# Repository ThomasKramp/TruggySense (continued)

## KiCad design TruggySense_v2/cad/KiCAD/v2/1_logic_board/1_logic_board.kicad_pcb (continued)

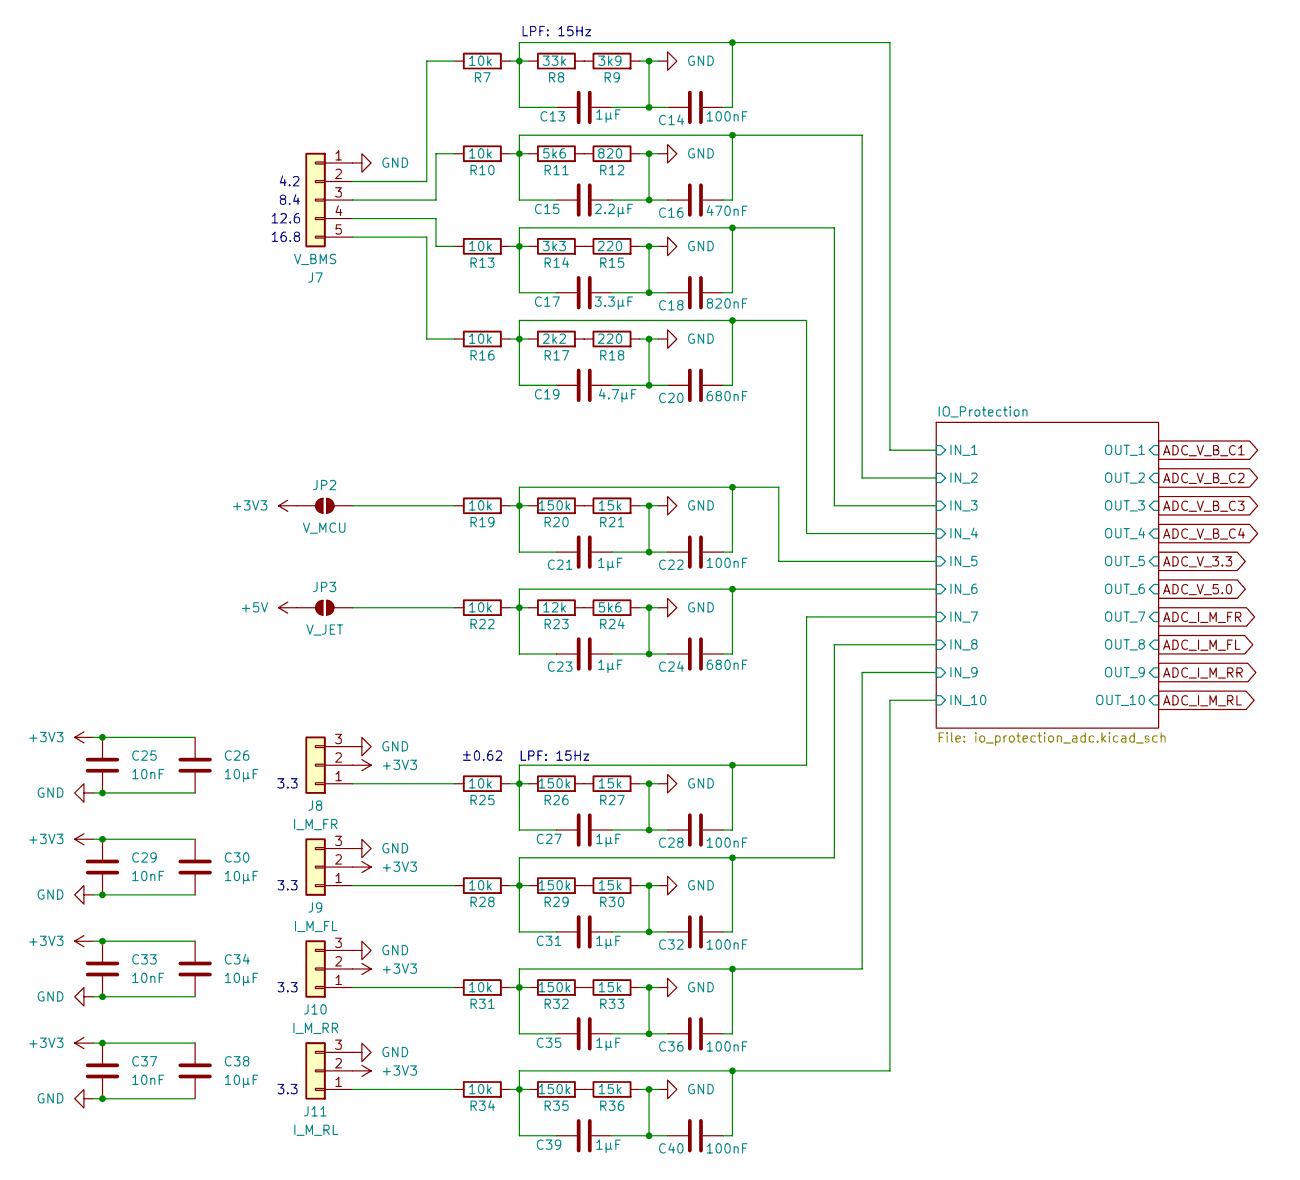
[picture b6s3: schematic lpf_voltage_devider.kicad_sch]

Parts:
C13, C21, C23, C27, C31, C35, C39: 1µF; C_0805_2012Metric_Pad1.18x1.45mm_HandSolder
C14, C22, C28, C32, C36, C40: 100nF; C_0805_2012Metric_Pad1.18x1.45mm_HandSolder
C15: 2.2µF; C_0805_2012Metric_Pad1.18x1.45mm_HandSolder
C16: 470nF; C_0805_2012Metric_Pad1.18x1.45mm_HandSolder
C17: 3.3µF; C_0805_2012Metric_Pad1.18x1.45mm_HandSolder
C18: 820nF; C_0805_2012Metric_Pad1.18x1.45mm_HandSolder
C19: 4.7µF; C_0805_2012Metric_Pad1.18x1.45mm_HandSolder
C20, C24: 680nF; C_0805_2012Metric_Pad1.18x1.45mm_HandSolder
C25, C29, C33, C37: 10nF; C_0805_2012Metric_Pad1.18x1.45mm_HandSolder
C26, C30, C34, C38: 10µF; C_0805_2012Metric_Pad1.18x1.45mm_HandSolder
J7: V_BMS; JST_XH_B5B-XH-A_1x05_P2.50mm_Vertical
J8: I_M_FR; JST_XH_B3B-XH-A_1x03_P2.50mm_Vertical
J9: I_M_FL; JST_XH_B3B-XH-A_1x03_P2.50mm_Vertical
J10: I_M_RR; JST_XH_B3B-XH-A_1x03_P2.50mm_Vertical
J11: I_M_RL; JST_XH_B3B-XH-A_1x03_P2.50mm_Vertical
JP2: V_MCU; SolderJumper-2_P1.3mm_Open_RoundedPad1.0x1.5mm
JP3: V_JET; SolderJumper-2_P1.3mm_Open_RoundedPad1.0x1.5mm
R7, R10, R13, R16, R19, R22, R25, R28, R31, R34: 10k; R_0805_2012Metric_Pad1.20x1.40mm_HandSolder
R8: 33k; R_0805_2012Metric_Pad1.20x1.40mm_HandSolder
R9: 3k9; R_0805_2012Metric_Pad1.20x1.40mm_HandSolder
R11, R24: 5k6; R_0805_2012Metric_Pad1.20x1.40mm_HandSolder
R12: 820; R_0805_2012Metric_Pad1.20x1.40mm_HandSolder
R14: 3k3; R_0805_2012Metric_Pad1.20x1.40mm_HandSolder
R15, R18: 220; R_0805_2012Metric_Pad1.20x1.40mm_HandSolder
R17: 2k2; R_0805_2012Metric_Pad1.20x1.40mm_HandSolder
R20, R26, R29, R32, R35: 150k; R_0805_2012Metric_Pad1.20x1.40mm_HandSolder
R21, R27, R30, R33, R36: 15k; R_0805_2012Metric_Pad1.20x1.40mm_HandSolder
R23: 12k; R_0805_2012Metric_Pad1.20x1.40mm_HandSolder

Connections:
+3V3: C25.1, C26.1, C29.1, C30.1, C33.1, C34.1, C37.1, C38.1, J8.2, J9.2, J10.2, J11.2, JP2.2 (B); also elsewhere on the board
+5V: JP3.2 (B); also elsewhere on the board
/ADC/IO_Protection/IN_1: C13.1, C14.1, R7.2, R8.1; also elsewhere on the board
/ADC/IO_Protection/IN_2: C15.1, C16.1, R10.2, R11.1; also elsewhere on the board
/ADC/IO_Protection/IN_3: C17.1, C18.1, R13.2, R14.1; also elsewhere on the board
/ADC/IO_Protection/IN_4: C19.1, C20.1, R16.2, R17.1; also elsewhere on the board
/ADC/IO_Protection/IN_5: C21.2, C22.1, R19.2, R20.1; also elsewhere on the board
/ADC/IO_Protection/IN_6: C23.2, C24.1, R22.2, R23.1; also elsewhere on the board
/ADC/IO_Protection/IN_7: C27.1, C28.1, R25.2, R26.1; also elsewhere on the board
/ADC/IO_Protection/IN_8: C31.1, C32.1, R28.2, R29.1; also elsewhere on the board
/ADC/IO_Protection/IN_9: C35.1, C36.1, R31.2, R32.1; also elsewhere on the board
/ADC/IO_Protection/IN_10: C39.1, C40.1, R34.2, R35.1; also elsewhere on the board
GND: C13.2, C14.2, C15.2, C16.2, C17.2, C18.2, C19.2, C20.2, C21.1, C22.2, C23.1, C24.2, C25.2, C26.2, C27.2, C28.2, C29.2, C30.2, C31.2, C32.2, C33.2, C34.2, C35.2, C36.2, C37.2, C38.2, C39.2, C40.2, J7.1, J8.3, J9.3, J10.3, J11.3, R9.2, R12.2, R15.2, R18.2, R21.2, R24.2, R27.2, R30.2, R33.2, R36.2; also elsewhere on the board
unnamed: J7.2, R7.1
unnamed: J7.3, R10.1
unnamed: J7.4, R13.1
unnamed: J7.5, R16.1
unnamed: J8.1, R25.1
unnamed: J9.1, R28.1
unnamed: J10.1, R31.1
unnamed: J11.1, R34.1
unnamed: JP2.1 (A), R19.1
unnamed: JP3.1 (A), R22.1
unnamed: R8.2, R9.1
unnamed: R11.2, R12.1
unnamed: R14.2, R15.1
unnamed: R17.2, R18.1
unnamed: R20.2, R21.1
unnamed: R23.2, R24.1
unnamed: R26.2, R27.1
unnamed: R29.2, R30.1
unnamed: R32.2, R33.1
unnamed: R35.2, R36.1

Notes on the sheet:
8.4
LPF: 15Hz
3.3
16.8
±0.62
12.6
4.2

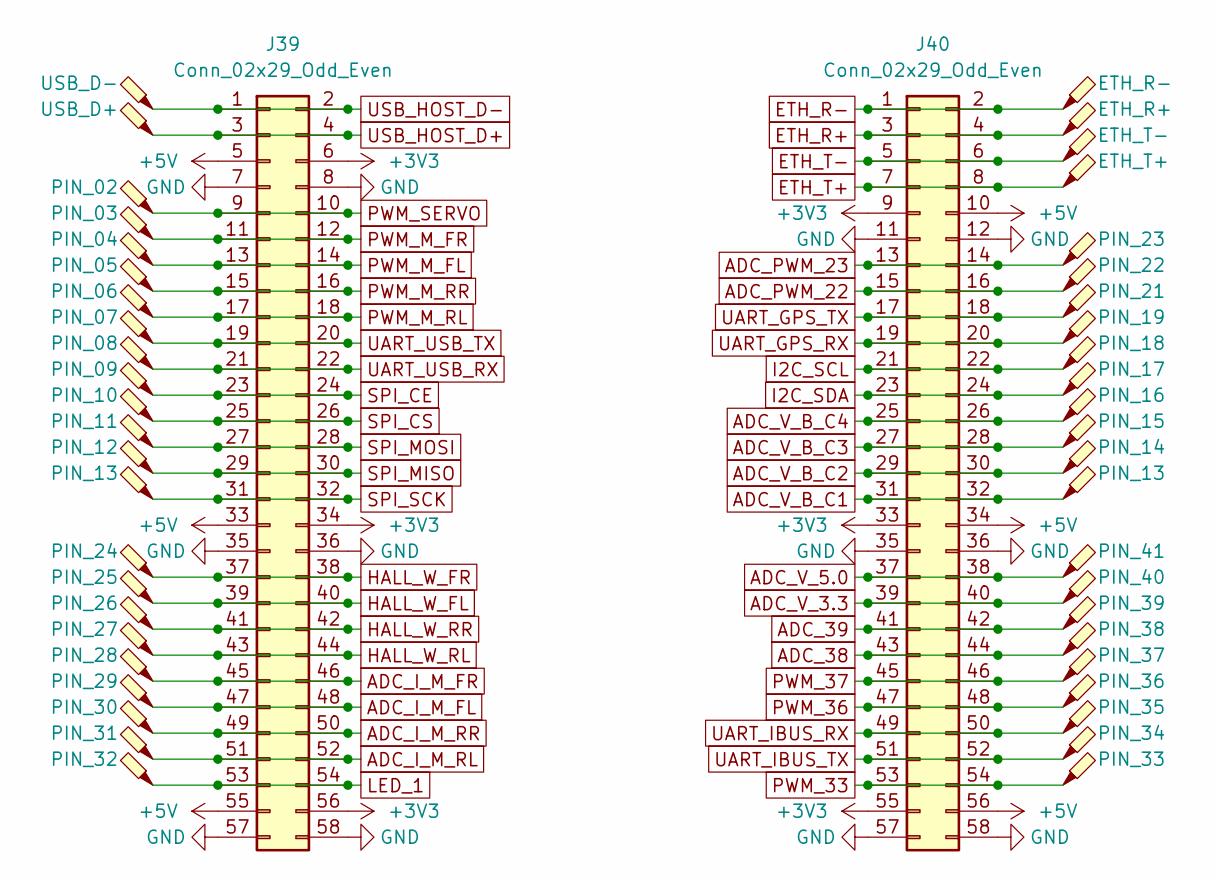
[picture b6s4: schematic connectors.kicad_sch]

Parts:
J39, J40: Conn_02x29_Odd_Even; PinHeader_2x29_P2.54mm_Vertical
TP1: USB_D-; Pin_D1.3mm_L11.0mm
TP2: ETH_R-; Pin_D1.3mm_L11.0mm
TP3: USB_D+; Pin_D1.3mm_L11.0mm
TP4: ETH_R+; Pin_D1.3mm_L11.0mm
TP5: ETH_T-; Pin_D1.3mm_L11.0mm
TP6: ETH_T+; Pin_D1.3mm_L11.0mm
TP7: PIN_02; Pin_D1.3mm_L11.0mm
TP8: PIN_03; Pin_D1.3mm_L11.0mm
TP9: PIN_04; Pin_D1.3mm_L11.0mm
TP10: PIN_23; Pin_D1.3mm_L11.0mm
TP11: PIN_05; Pin_D1.3mm_L11.0mm
TP12: PIN_22; Pin_D1.3mm_L11.0mm
TP13: PIN_06; Pin_D1.3mm_L11.0mm
TP14: PIN_21; Pin_D1.3mm_L11.0mm
TP15: PIN_07; Pin_D1.3mm_L11.0mm
TP16: PIN_19; Pin_D1.3mm_L11.0mm
TP17: PIN_08; Pin_D1.3mm_L11.0mm
TP18: PIN_18; Pin_D1.3mm_L11.0mm
TP19: PIN_09; Pin_D1.3mm_L11.0mm
TP20: PIN_17; Pin_D1.3mm_L11.0mm
TP21: PIN_10; Pin_D1.3mm_L11.0mm
TP22: PIN_16; Pin_D1.3mm_L11.0mm
TP23: PIN_11; Pin_D1.3mm_L11.0mm
TP24: PIN_15; Pin_D1.3mm_L11.0mm
TP25: PIN_12; Pin_D1.3mm_L11.0mm
TP26: PIN_14; Pin_D1.3mm_L11.0mm
TP27, TP28: PIN_13; Pin_D1.3mm_L11.0mm
TP29: PIN_24; Pin_D1.3mm_L11.0mm
TP30: PIN_41; Pin_D1.3mm_L11.0mm
TP31: PIN_25; Pin_D1.3mm_L11.0mm
TP32: PIN_40; Pin_D1.3mm_L11.0mm
TP33: PIN_26; Pin_D1.3mm_L11.0mm
TP34: PIN_39; Pin_D1.3mm_L11.0mm
TP35: PIN_27; Pin_D1.3mm_L11.0mm
TP36: PIN_38; Pin_D1.3mm_L11.0mm
TP37: PIN_28; Pin_D1.3mm_L11.0mm
TP38: PIN_37; Pin_D1.3mm_L11.0mm
TP39: PIN_29; Pin_D1.3mm_L11.0mm
TP40: PIN_36; Pin_D1.3mm_L11.0mm
TP41: PIN_30; Pin_D1.3mm_L11.0mm
TP42: PIN_35; Pin_D1.3mm_L11.0mm
TP43: PIN_31; Pin_D1.3mm_L11.0mm
TP44: PIN_34; Pin_D1.3mm_L11.0mm
TP45: PIN_32; Pin_D1.3mm_L11.0mm
TP46: PIN_33; Pin_D1.3mm_L11.0mm

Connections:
+3V3: J39.6, J39.34, J39.56, J40.9, J40.33, J40.55; also elsewhere on the board
+5V: J39.5, J39.33, J39.55, J40.10, J40.34, J40.56; also elsewhere on the board
ADC_38: J40.43, J40.44, TP36.1; also elsewhere on the board
ADC_39: J40.41, J40.42, TP34.1; also elsewhere on the board
ADC_I_M_FL: J39.47, J39.48, TP39.1; also elsewhere on the board
ADC_I_M_FR: J39.45, J39.46, TP37.1; also elsewhere on the board
ADC_I_M_RL: J39.51, J39.52, TP43.1; also elsewhere on the board
ADC_I_M_RR: J39.49, J39.50, TP41.1; also elsewhere on the board
ADC_PWM_22: J40.15, J40.16, TP12.1; also elsewhere on the board
ADC_PWM_23: J40.13, J40.14, TP10.1; also elsewhere on the board
ADC_V_3.3: J40.39, J40.40, TP32.1; also elsewhere on the board
ADC_V_5.0: J40.37, J40.38, TP30.1; also elsewhere on the board
ADC_V_B_C1: J40.31, J40.32, TP28.1; also elsewhere on the board
ADC_V_B_C2: J40.29, J40.30, TP26.1; also elsewhere on the board
ADC_V_B_C3: J40.27, J40.28, TP24.1; also elsewhere on the board
ADC_V_B_C4: J40.25, J40.26, TP22.1; also elsewhere on the board
ETH_R+: J40.3, J40.4, TP4.1; also elsewhere on the board
ETH_R-: J40.1, J40.2, TP2.1; also elsewhere on the board
ETH_T+: J40.7, J40.8, TP6.1; also elsewhere on the board
ETH_T-: J40.5, J40.6, TP5.1; also elsewhere on the board
GND: J39.7, J39.8, J39.35, J39.36, J39.57, J39.58, J40.11, J40.12, J40.35, J40.36, J40.57, J40.58; also elsewhere on the board
HALL_W_FL: J39.39, J39.40, TP31.1; also elsewhere on the board
HALL_W_FR: J39.37, J39.38, TP29.1; also elsewhere on the board
HALL_W_RL: J39.43, J39.44, TP35.1; also elsewhere on the board
HALL_W_RR: J39.41, J39.42, TP33.1; also elsewhere on the board
I2C_SCL: J40.21, J40.22, TP18.1; also elsewhere on the board
I2C_SDA: J40.23, J40.24, TP20.1; also elsewhere on the board
LED_1: J39.53, J39.54, TP45.1; also elsewhere on the board
PWM_33: J40.53, J40.54, TP46.1; also elsewhere on the board
PWM_36: J40.47, J40.48, TP40.1; also elsewhere on the board
PWM_37: J40.45, J40.46, TP38.1; also elsewhere on the board
PWM_M_FL: J39.13, J39.14, TP9.1; also elsewhere on the board
PWM_M_FR: J39.11, J39.12, TP8.1; also elsewhere on the board
PWM_M_RL: J39.17, J39.18, TP13.1; also elsewhere on the board
PWM_M_RR: J39.15, J39.16, TP11.1; also elsewhere on the board
PWM_SERVO: J39.9, J39.10, TP7.1; also elsewhere on the board
SPI_CE: J39.23, J39.24, TP19.1; also elsewhere on the board
SPI_CS: J39.25, J39.26, TP21.1; also elsewhere on the board
SPI_MISO: J39.29, J39.30, TP25.1; also elsewhere on the board
SPI_MOSI: J39.27, J39.28, TP23.1; also elsewhere on the board
SPI_SCK: J39.31, J39.32, TP27.1; also elsewhere on the board
UART_GPS_RX: J40.19, J40.20, TP16.1; also elsewhere on the board
UART_GPS_TX: J40.17, J40.18, TP14.1; also elsewhere on the board
UART_IBUS_RX: J40.49, J40.50, TP42.1; also elsewhere on the board
UART_IBUS_TX: J40.51, J40.52, TP44.1; also elsewhere on the board
UART_USB_RX: J39.21, J39.22, TP17.1; also elsewhere on the board
UART_USB_TX: J39.19, J39.20, TP15.1; also elsewhere on the board
USB_HOST_D+: J39.3, J39.4, TP3.1; also elsewhere on the board
USB_HOST_D-: J39.1, J39.2, TP1.1; also elsewhere on the board

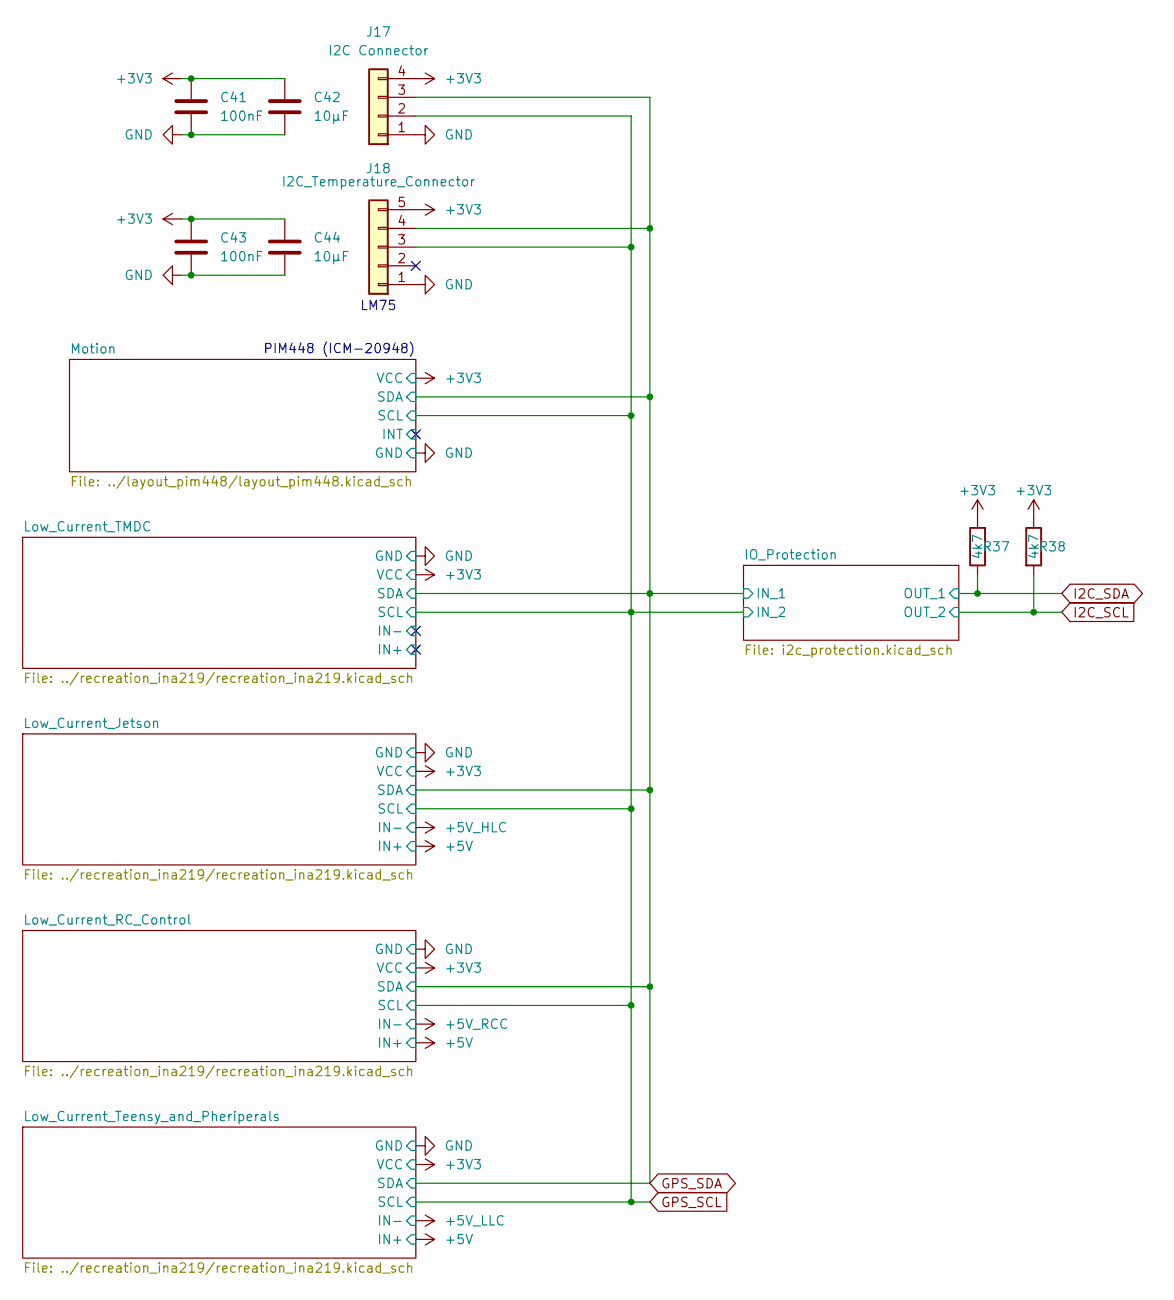
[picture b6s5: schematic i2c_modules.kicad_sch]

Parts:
C41, C43: 100nF; C_0805_2012Metric_Pad1.18x1.45mm_HandSolder
C42, C44: 10µF; C_0805_2012Metric_Pad1.18x1.45mm_HandSolder
J17: I2C Connector; JST_XH_B4B-XH-A_1x04_P2.50mm_Vertical
J18: I2C_Temperature_Connector; JST_XH_B5B-XH-A_1x05_P2.50mm_Vertical
R37, R38: 4k7; R_0805_2012Metric_Pad1.20x1.40mm_HandSolder

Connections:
+3V3: C41.1, C42.1, C43.1, C44.1, J17.4, J18.5, R37.2, R38.1; also elsewhere on the board
GND: C41.2, C42.2, C43.2, C44.2, J17.1, J18.1; also elsewhere on the board
GPS_SCL: J17.2, J18.3; also elsewhere on the board
GPS_SDA: J17.3, J18.4; also elsewhere on the board
I2C_SCL: R38.2; also elsewhere on the board
I2C_SDA: R37.1; also elsewhere on the board

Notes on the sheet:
PIM448 (ICM-20948)
LM75

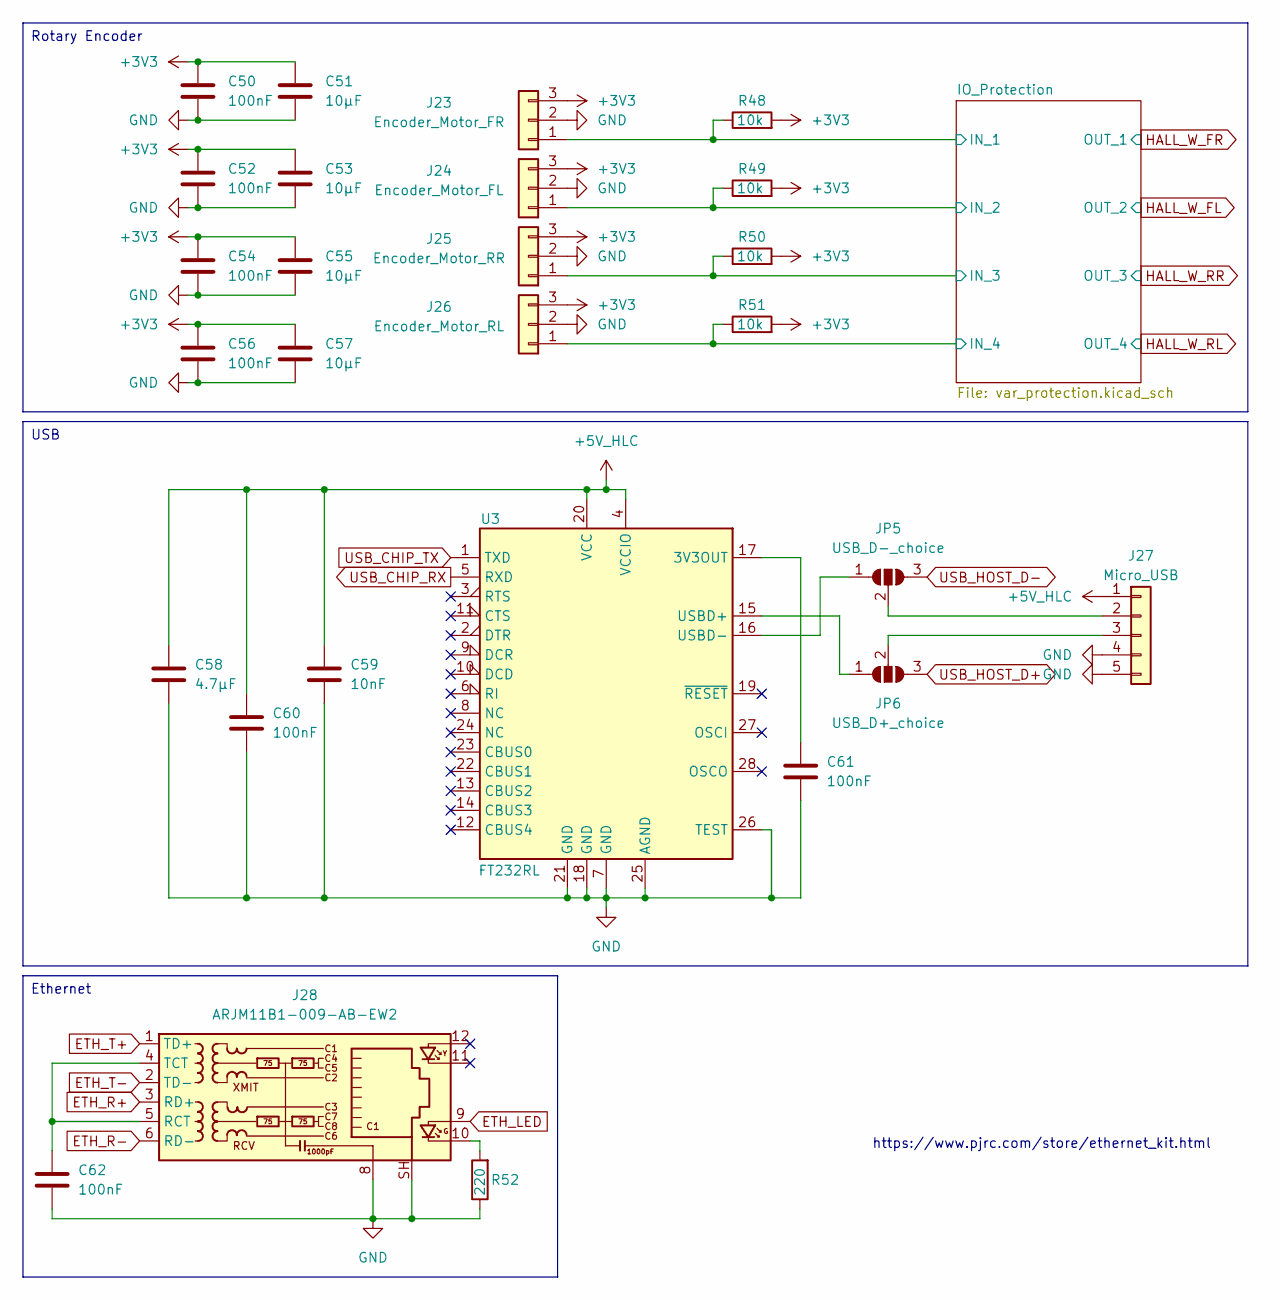
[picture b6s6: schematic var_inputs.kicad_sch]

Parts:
C50, C52, C54, C56, C60, C61, C62: 100nF; C_0805_2012Metric_Pad1.18x1.45mm_HandSolder
C51, C53, C55, C57: 10µF; C_0805_2012Metric_Pad1.18x1.45mm_HandSolder
C58: 4.7µF; C_0805_2012Metric_Pad1.18x1.45mm_HandSolder
C59: 10nF; C_0805_2012Metric_Pad1.18x1.45mm_HandSolder
J23: Encoder_Motor_FR; JST_XH_B3B-XH-A_1x03_P2.50mm_Vertical
J24: Encoder_Motor_FL; JST_XH_B3B-XH-A_1x03_P2.50mm_Vertical
J25: Encoder_Motor_RR; JST_XH_B3B-XH-A_1x03_P2.50mm_Vertical
J26: Encoder_Motor_RL; JST_XH_B3B-XH-A_1x03_P2.50mm_Vertical
J27: Micro_USB; PinHeader_1x05_P2.54mm_Vertical
J28: ARJM11B1-009-AB-EW2; CONN12_ARJM11B1-009-AB-EW2_ABR
JP5: USB_D-_choice; SolderJumper-3_P2.0mm_Open_TrianglePad1.0x1.5mm_NumberLabels
JP6: USB_D+_choice; SolderJumper-3_P2.0mm_Open_TrianglePad1.0x1.5mm_NumberLabels
R48, R49, R50, R51: 10k; R_0805_2012Metric_Pad1.20x1.40mm_HandSolder
R52: 220; R_0805_2012Metric_Pad1.20x1.40mm_HandSolder
U3: FT232RL; SSOP-28_5.3x10.2mm_P0.65mm

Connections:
+3V3: C50.1, C51.1, C52.1, C53.1, C54.1, C55.1, C56.1, C57.1, J23.3, J24.3, J25.3, J26.3, R48.2, R49.2, R50.2, R51.2; also elsewhere on the board
+5V_HLC: C58.1, C59.1, C60.1, J27.1, U3.4 (VCCIO), U3.20 (VCC); also elsewhere on the board
/Various Inputs/IO_Protection/IN_1: J23.1, R48.1; also elsewhere on the board
/Various Inputs/IO_Protection/IN_2: J24.1, R49.1; also elsewhere on the board
/Various Inputs/IO_Protection/IN_3: J25.1, R50.1; also elsewhere on the board
/Various Inputs/IO_Protection/IN_4: J26.1, R51.1; also elsewhere on the board
ETH_LED: J28.9; also elsewhere on the board
ETH_R+: J28.3 (RD+); also elsewhere on the board
ETH_R-: J28.6 (RD-); also elsewhere on the board
ETH_T+: J28.1 (TD+); also elsewhere on the board
ETH_T-: J28.2 (TD-); also elsewhere on the board
GND: C50.2, C51.2, C52.2, C53.2, C54.2, C55.2, C56.2, C57.2, C58.2, C59.2, C60.2, C61.2, C62.2, J23.2, J24.2, J25.2, J26.2, J27.4, J27.5, J28.8, J28.SH, R52.1, U3.7 (GND), U3.18 (GND), U3.21 (GND), U3.25 (AGND), U3.26 (TEST); also elsewhere on the board
unnamed: J27.2, JP5.2 (C)
unnamed: J27.3, JP6.2 (C)
unnamed: J28.10, R52.2
unnamed: C62.1, J28.4 (TCT), J28.5 (RCT)
unnamed: JP5.1 (A), U3.16 (USBD-)
unnamed: JP6.1 (A), U3.15 (USBD+)
unnamed: C61.1, U3.17 (3V3OUT)
USB_CHIP_RX: U3.5 (RXD); also elsewhere on the board
USB_CHIP_TX: U3.1 (TXD); also elsewhere on the board
USB_HOST_D+: JP6.3 (B); also elsewhere on the board
USB_HOST_D-: JP5.3 (B); also elsewhere on the board

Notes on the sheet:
https://www.pjrc.com/store/ethernet_kit.html
Ethernet
USB
Rotary Encoder

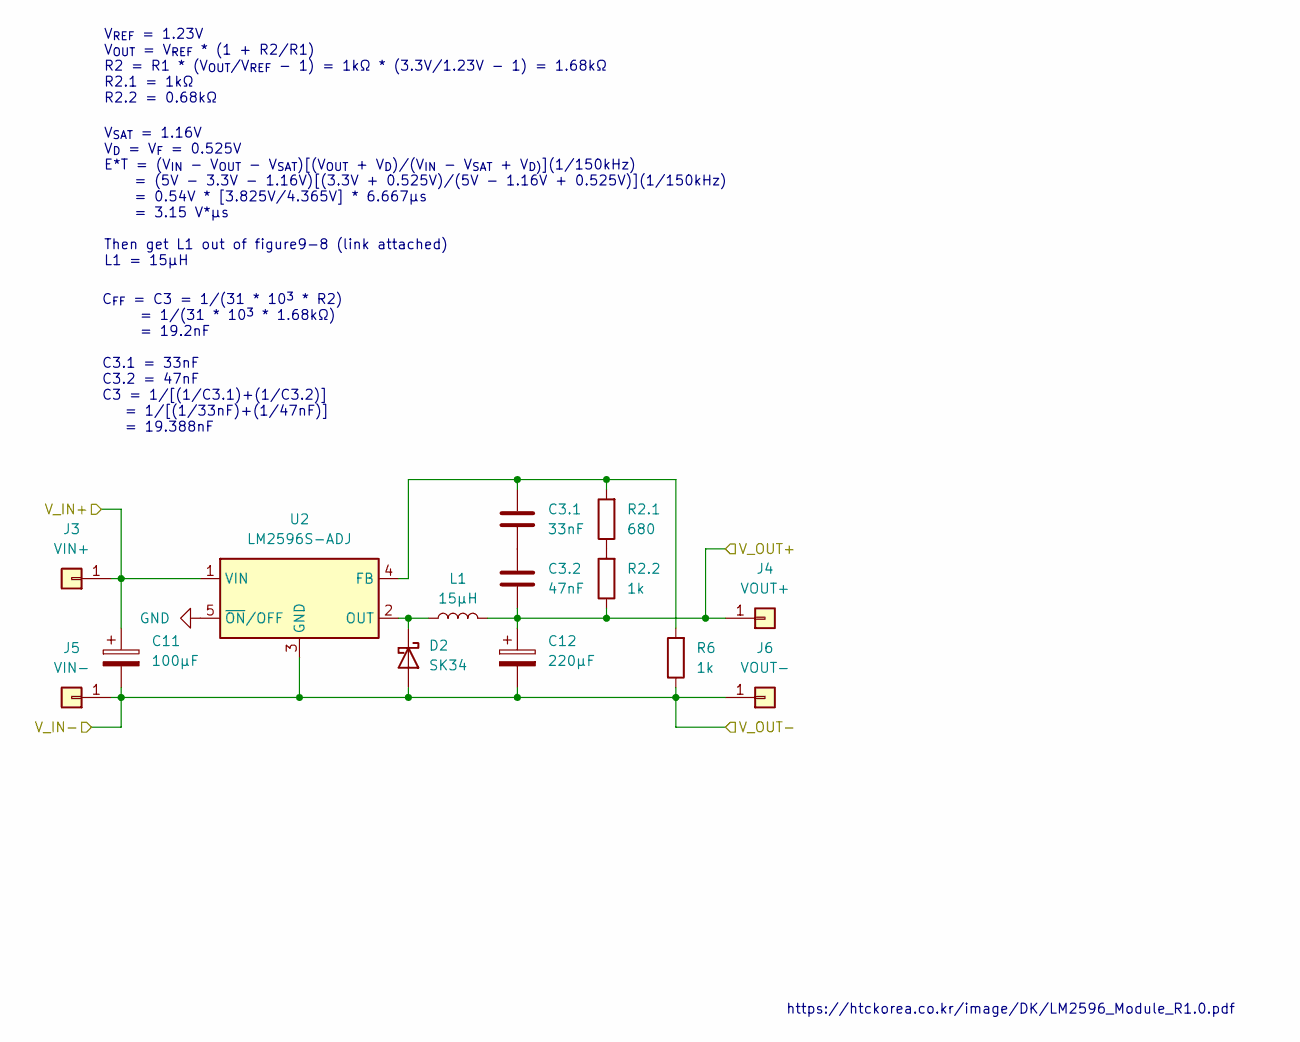
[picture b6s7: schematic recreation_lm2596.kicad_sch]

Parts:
C3.1: 33nF; C_0805_2012Metric_Pad1.18x1.45mm_HandSolder
C3.2: 47nF; C_0805_2012Metric_Pad1.18x1.45mm_HandSolder
C11: 100µF; CP_Radial_D5.0mm_P2.00mm
C12: 220µF; CP_Radial_D6.3mm_P2.50mm
D2: SK34; D_SMA_Handsoldering
J3: VIN+; PinHeader_1x01_P2.54mm_Vertical
J4: VOUT+; PinHeader_1x01_P2.54mm_Vertical
J5: VIN-; PinHeader_1x01_P2.54mm_Vertical
J6: VOUT-; PinHeader_1x01_P2.54mm_Vertical
L1: 15µH; 29153C
R2.1: 680; R_0805_2012Metric_Pad1.20x1.40mm_HandSolder
R2.2, R6: 1k; R_0805_2012Metric_Pad1.20x1.40mm_HandSolder
U2: LM2596S-ADJ; TO-263-5_TabPin3

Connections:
+3V3_CONV: C3.2.2, C12.1, J4.1, L1.2, R2.2.1; also elsewhere on the board
+5V_LLC: C11.1, J3.1, U2.1 (VIN); also elsewhere on the board
GND: C11.2, C12.2, D2.2 (A), J5.1, J6.1, R6.1, U2.3 (GND), U2.5 (~ON/OFF); also elsewhere on the board
unnamed: C3.1.2, C3.2.1
unnamed: D2.1 (K), L1.1, U2.2 (OUT)
unnamed: R2.1.1, R2.2.2
unnamed: C3.1.1, R2.1.2, R6.2, U2.4 (FB)

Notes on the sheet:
V_{SAT} = 1.16V V_{D} = V_{F} = 0.525V E*T = (V_{IN} - V_{OUT} - V_{SAT})[(V_{OUT} + V_{D})/(V_{IN} - V_{SAT} + V_{D)}](1/150kHz) = (5V - 3.3V - 1.16V)[(3.3V + 0.525V)/(5V - 1.16V + 0.525V)](1/150kHz) = 0.54V * [3.825V/4.365V] * 6.667µs = 3.15 V*µs Then get L1 out of figure9-8 (link attached) L1 = 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
V_{REF} = 1.23V V_{OUT} = V_{REF} * (1 + R2/R1) R2 = R1 * (V_{OUT}/V_{REF} - 1) = 1kΩ * (3.3V/1.23V - 1) = 1.68kΩ R2.1 = 1kΩ R2.2 = 0.68kΩ
https://htckorea.co.kr/image/DK/LM2596_Module_R1.0.pdf
C_{FF} = C3 = 1/(31 * 10^{3} * R2) = 1/(31 * 10^{3} * 1.68kΩ) = 19.2nF C3.1 = 33nF C3.2 = 47nF C3 = 1/[(1/C3.1)+(1/C3.2)] = 1/[(1/33nF)+(1/47nF)] = 19.388nF

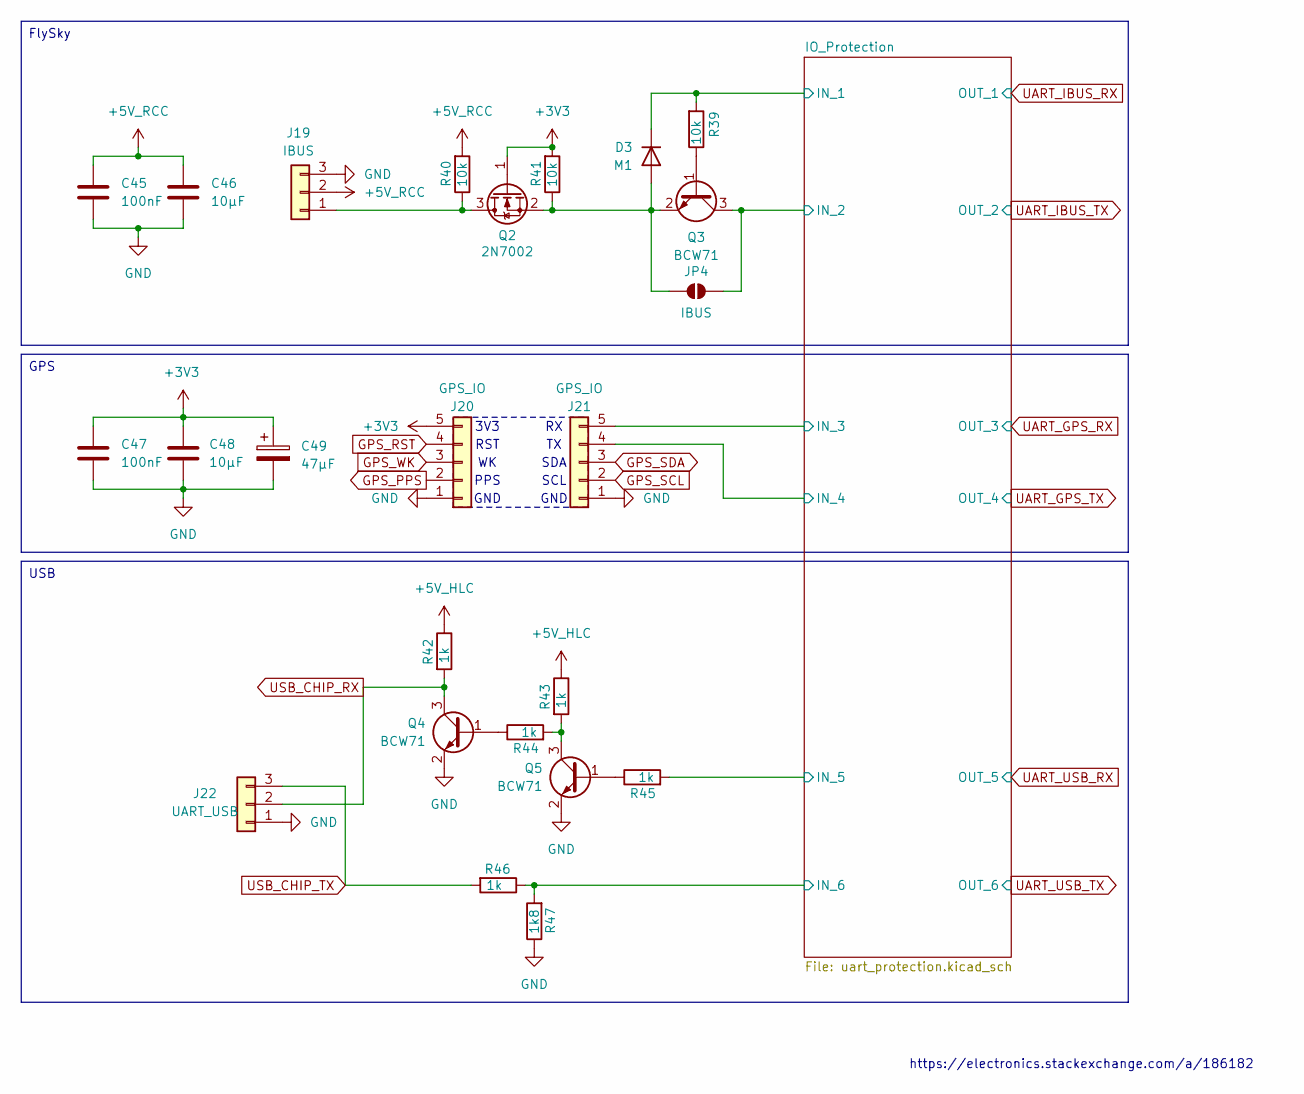
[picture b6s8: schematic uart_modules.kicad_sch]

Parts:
C45, C47: 100nF; C_0805_2012Metric_Pad1.18x1.45mm_HandSolder
C46, C48: 10µF; C_0805_2012Metric_Pad1.18x1.45mm_HandSolder
C49: 47µF; CP_Radial_D8.0mm_P3.50mm
D3: M1; D_SMA_Handsoldering
J19: IBUS; JST_XH_B3B-XH-A_1x03_P2.50mm_Vertical
J20, J21: GPS_IO; PinHeader_1x05_P2.54mm_Vertical
J22: UART_USB; PinHeader_1x03_P2.54mm_Vertical
JP4: IBUS; SolderJumper-2_P1.3mm_Open_RoundedPad1.0x1.5mm
Q2: 2N7002; SOT-23
Q3, Q4, Q5: BCW71; SOT-23
R39, R40, R41: 10k; R_0805_2012Metric_Pad1.20x1.40mm_HandSolder
R42, R43, R44, R45, R46: 1k; R_0805_2012Metric_Pad1.20x1.40mm_HandSolder
R47: 1k8; R_0805_2012Metric_Pad1.20x1.40mm_HandSolder

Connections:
+3V3: C47.1, C48.1, C49.1, J20.5, Q2.1 (G), R41.2; also elsewhere on the board
+5V_HLC: R42.1, R43.1; also elsewhere on the board
+5V_RCC: C45.1, C46.1, J19.2, R40.2; also elsewhere on the board
/UART/IO_Protection/IN_1: D3.1 (K), R39.2; also elsewhere on the board
/UART/IO_Protection/IN_2: JP4.1 (A), Q3.3 (C); also elsewhere on the board
/UART/IO_Protection/IN_3: J21.5; also elsewhere on the board
/UART/IO_Protection/IN_4: J21.4; also elsewhere on the board
/UART/IO_Protection/IN_5: R45.2; also elsewhere on the board
/UART/IO_Protection/IN_6: R46.1, R47.2; also elsewhere on the board
GND: C45.2, C46.2, C47.2, C48.2, C49.2, J19.3, J20.1, J21.1, J22.1, Q4.2 (E), Q5.2 (E), R47.1; also elsewhere on the board
GPS_PPS: J20.2
GPS_RST: J20.4
GPS_SCL: J21.2; also elsewhere on the board
GPS_SDA: J21.3; also elsewhere on the board
GPS_WK: J20.3
unnamed: D3.2 (A), JP4.2 (B), Q2.2 (S), Q3.2 (E), R41.1
unnamed: J19.1, Q2.3 (D), R40.1
unnamed: Q3.1 (B), R39.1
unnamed: Q4.1 (B), R44.1
unnamed: Q5.1 (B), R45.1
unnamed: Q5.3 (C), R43.2, R44.2
USB_CHIP_RX: J22.2, Q4.3 (C), R42.2; also elsewhere on the board
USB_CHIP_TX: J22.3, R46.2; also elsewhere on the board

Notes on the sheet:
GND
SCL
PPS
https://electronics.stackexchange.com/a/186182
RST
3V3
SDA
GPS
USB
FlySky

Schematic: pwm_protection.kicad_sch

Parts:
C76, C78, C80, C82, C84: 100nF; C_0805_2012Metric_Pad1.18x1.45mm_HandSolder
C77, C79, C81, C83, C85: 470µF; CP_Radial_D10.0mm_P5.00mm
JP15, JP17, JP19, JP21, JP23: PWM_VCC; SolderJumper-2_P1.3mm_Open_RoundedPad1.0x1.5mm
JP16, JP18, JP20, JP22, JP24: PWM_GND; SolderJumper-2_P1.3mm_Open_RoundedPad1.0x1.5mm

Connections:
+5V_RCC: JP15.1 (A), JP17.1 (A), JP19.1 (A), JP21.1 (A), JP23.1 (A); also elsewhere on the board
/PWM/IO_Protection/GND_OUT_1: C76.2, C77.2, JP16.1 (A); also elsewhere on the board
/PWM/IO_Protection/GND_OUT_2: C78.2, C79.2, JP18.1 (A); also elsewhere on the board
/PWM/IO_Protection/GND_OUT_3: C80.2, C81.2, JP20.1 (A); also elsewhere on the board
/PWM/IO_Protection/GND_OUT_4: C82.2, C83.2, JP22.1 (A); also elsewhere on the board
/PWM/IO_Protection/GND_OUT_5: C84.2, C85.2, JP24.1 (A); also elsewhere on the board
/PWM/IO_Protection/VCC_OUT_1: C76.1, C77.1, JP15.2 (B); also elsewhere on the board
/PWM/IO_Protection/VCC_OUT_2: C78.1, C79.1, JP17.2 (B); also elsewhere on the board
/PWM/IO_Protection/VCC_OUT_3: C80.1, C81.1, JP19.2 (B); also elsewhere on the board
/PWM/IO_Protection/VCC_OUT_4: C82.1, C83.1, JP21.2 (B); also elsewhere on the board
/PWM/IO_Protection/VCC_OUT_5: C84.1, C85.1, JP23.2 (B); also elsewhere on the board
GND: JP16.2 (B), JP18.2 (B), JP20.2 (B), JP22.2 (B), JP24.2 (B); also elsewhere on the board

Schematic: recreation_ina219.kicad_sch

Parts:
C65: 100nF; C_0805_2012Metric_Pad1.18x1.45mm_HandSolder
C66: 4.7µF; C_0805_2012Metric_Pad1.18x1.45mm_HandSolder
J30: IN; TerminalBlock_Phoenix_PT-1,5-2-3.5-H_1x02_P3.50mm_Horizontal
J31: INA_IO; PinHeader_1x06_P2.54mm_Vertical
JP7: A1; SolderJumper-2_P1.3mm_Open_RoundedPad1.0x1.5mm
JP8: A0; SolderJumper-2_P1.3mm_Open_RoundedPad1.0x1.5mm
R53, R54, R56, R57: 10k; R_0805_2012Metric_Pad1.20x1.40mm_HandSolder
R55: 100m; R_2512_6332Metric_Pad1.40x3.35mm_HandSolder
U4: INA219AxDCN; SOT-23-8

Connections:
+3V3: C65.1, C66.1, J31.1, JP7.2 (B), JP8.2 (B), R53.1, R54.1, U4.4 (VS); also elsewhere on the board
/I2C/Low_Current_TMDC/IN+: J30.1, J31.6, R55.1, U4.1 (IN+)
/I2C/Low_Current_TMDC/IN-: J30.2, J31.5, R55.2, U4.2 (IN-)
GND: C65.2, C66.2, J31.2, R56.2, R57.2, U4.3 (GND); also elsewhere on the board
GPS_SCL: J31.3, R54.2, U4.5 (SCL); also elsewhere on the board
GPS_SDA: J31.4, R53.2, U4.6 (SDA); also elsewhere on the board
unnamed: JP7.1 (A), R56.1, U4.8 (A1)
unnamed: JP8.1 (A), R57.1, U4.7 (A0)

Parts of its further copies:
C67, C69, C71: 100nF; C_0805_2012Metric_Pad1.18x1.45mm_HandSolder
C68, C70, C72: 4.7µF; C_0805_2012Metric_Pad1.18x1.45mm_HandSolder
J32, J34, J36: IN; TerminalBlock_Phoenix_PT-1,5-2-3.5-H_1x02_P3.50mm_Horizontal
J33, J35, J37: INA_IO; PinHeader_1x06_P2.54mm_Vertical
JP9, JP11, JP13: A1; SolderJumper-2_P1.3mm_Open_RoundedPad1.0x1.5mm
JP10, JP12, JP14: A0; SolderJumper-2_P1.3mm_Open_RoundedPad1.0x1.5mm
R58, R59, R61, R62, R63, R64, R66, R67, R68, R69, R71, R72: 10k; R_0805_2012Metric_Pad1.20x1.40mm_HandSolder
R60, R65, R70: 100m; R_2512_6332Metric_Pad1.40x3.35mm_HandSolder
U5, U6, U7: INA219AxDCN; SOT-23-8

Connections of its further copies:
+3V3: C67.1, C68.1, C69.1, C70.1, C71.1, C72.1, J33.1, J35.1, J37.1, JP9.2 (B), JP10.2 (B), JP11.2 (B), JP12.2 (B), JP13.2 (B), JP14.2 (B), R58.1, R59.1, R63.1, R64.1, R68.1, R69.1, U5.4 (VS), U6.4 (VS), U7.4 (VS); also elsewhere on the board
+5V: J32.1, J33.6, J34.1, J35.6, J36.1, J37.6, R60.1, R65.1, R70.1, U5.1 (IN+), U6.1 (IN+), U7.1 (IN+); also elsewhere on the board
+5V_HLC: J32.2, J33.5, R60.2, U5.2 (IN-); also elsewhere on the board
+5V_LLC: J36.2, J37.5, R70.2, U7.2 (IN-); also elsewhere on the board
+5V_RCC: J34.2, J35.5, R65.2, U6.2 (IN-); also elsewhere on the board
GND: C67.2, C68.2, C69.2, C70.2, C71.2, C72.2, J33.2, J35.2, J37.2, R61.2, R62.2, R66.2, R67.2, R71.2, R72.2, U5.3 (GND), U6.3 (GND), U7.3 (GND); also elsewhere on the board
GPS_SCL: J33.3, J35.3, J37.3, R59.2, R64.2, R69.2, U5.5 (SCL), U6.5 (SCL), U7.5 (SCL); also elsewhere on the board
GPS_SDA: J33.4, J35.4, J37.4, R58.2, R63.2, R68.2, U5.6 (SDA), U6.6 (SDA), U7.6 (SDA); also elsewhere on the board
unnamed: JP9.1 (A), R61.1, U5.8 (A1)
unnamed: JP10.1 (A), R62.1, U5.7 (A0)
unnamed: JP11.1 (A), R66.1, U6.8 (A1)
unnamed: JP12.1 (A), R67.1, U6.7 (A0)
unnamed: JP13.1 (A), R71.1, U7.8 (A1)
unnamed: JP14.1 (A), R72.1, U7.7 (A0)

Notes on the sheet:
https://learn.adafruit.com/adafruit-ina219-current-sensor-breakout/downloads

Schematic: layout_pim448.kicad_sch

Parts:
C63: 100nF; C_0805_2012Metric_Pad1.18x1.45mm_HandSolder
C64: 10µF; C_0805_2012Metric_Pad1.18x1.45mm_HandSolder
J29: Motion; PinHeader_1x05_P2.54mm_Vertical

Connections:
+3V3: C63.1, C64.1, J29.5; also elsewhere on the board
/I2C/Motion/INT: J29.2
GND: C63.2, C64.2, J29.1; also elsewhere on the board
GPS_SCL: J29.3; also elsewhere on the board
GPS_SDA: J29.4; also elsewhere on the board

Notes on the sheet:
https://mm.digikey.com/Volume0/opasdata/d220001/medias/docus/306/PIM448_Web.pdf

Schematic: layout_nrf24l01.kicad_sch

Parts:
C73: 100nF; C_0805_2012Metric_Pad1.18x1.45mm_HandSolder
C74: 10µF; C_0805_2012Metric_Pad1.18x1.45mm_HandSolder
C75: 47µF; CP_Radial_D8.0mm_P3.50mm
J38: nRF24L01; PinHeader_2x04_P2.54mm_Vertical

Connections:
+3V3: C73.1, C74.1, C75.1, J38.2; also elsewhere on the board
/SPI/IO_Protection/IN_1: J38.5; also elsewhere on the board
/SPI/IO_Protection/IN_2: J38.4; also elsewhere on the board
/SPI/IO_Protection/IN_3: J38.6; also elsewhere on the board
/SPI/IO_Protection/IN_4: J38.7; also elsewhere on the board
/SPI/IO_Protection/IN_5: J38.3; also elsewhere on the board
/SPI/Long_Range_Communication/IRQ: J38.8
GND: C73.2, C74.2, C75.2, J38.1; also elsewhere on the board

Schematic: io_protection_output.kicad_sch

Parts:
D14: LED; LED_PLCC-2_3.4x3.0mm_AK
F11: SMD0805B010TF; Fuse_0805_2012Metric_Pad1.15x1.40mm_HandSolder
JP25: PWM_FUSE; SolderJumper-2_P1.3mm_Open_RoundedPad1.0x1.5mm
R93: 470; R_0805_2012Metric_Pad1.20x1.40mm_HandSolder
R94: 330; R_0805_2012Metric_Pad1.20x1.40mm_HandSolder
R95: 1k; R_0805_2012Metric_Pad1.20x1.40mm_HandSolder
U13: VOS618A; SSOP-4_4.4x2.6mm_P1.27mm

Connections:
/PWM/IO_Protection/GND_OUT_1: R94.2, R95.2; also elsewhere on the board
/PWM/IO_Protection/OUT_1: D14.2 (A), R95.1, U13.3; also elsewhere on the board
/PWM/IO_Protection/VCC_OUT_1: F11.2, JP25.2 (B); also elsewhere on the board
GND: U13.2; also elsewhere on the board
unnamed: D14.1 (K), R94.1
unnamed: F11.1, JP25.1 (A), U13.4
unnamed: R93.2, U13.1
PWM_SERVO: R93.1; also elsewhere on the board

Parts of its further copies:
D15, D16, D17, D18: LED; LED_PLCC-2_3.4x3.0mm_AK
F12, F13, F14, F15: SMD0805B010TF; Fuse_0805_2012Metric_Pad1.15x1.40mm_HandSolder
JP26, JP27, JP28, JP29: PWM_FUSE; SolderJumper-2_P1.3mm_Open_RoundedPad1.0x1.5mm
R96, R99, R102, R105: 470; R_0805_2012Metric_Pad1.20x1.40mm_HandSolder
R97, R100, R103, R106: 330; R_0805_2012Metric_Pad1.20x1.40mm_HandSolder
R98, R101, R104, R107: 1k; R_0805_2012Metric_Pad1.20x1.40mm_HandSolder
U14, U15, U16, U17: VOS618A; SSOP-4_4.4x2.6mm_P1.27mm

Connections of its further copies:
/PWM/IO_Protection/GND_OUT_2: R97.2, R98.2; also elsewhere on the board
/PWM/IO_Protection/GND_OUT_3: R100.2, R101.2; also elsewhere on the board
/PWM/IO_Protection/GND_OUT_4: R103.2, R104.2; also elsewhere on the board
/PWM/IO_Protection/GND_OUT_5: R106.2, R107.2; also elsewhere on the board
/PWM/IO_Protection/OUT_2: D15.2 (A), R98.1, U14.3; also elsewhere on the board
/PWM/IO_Protection/OUT_3: D16.2 (A), R101.1, U15.3; also elsewhere on the board
/PWM/IO_Protection/OUT_4: D17.2 (A), R104.1, U16.3; also elsewhere on the board
/PWM/IO_Protection/OUT_5: D18.2 (A), R107.1, U17.3; also elsewhere on the board
/PWM/IO_Protection/VCC_OUT_2: F12.2, JP26.2 (B); also elsewhere on the board
/PWM/IO_Protection/VCC_OUT_3: F13.2, JP27.2 (B); also elsewhere on the board
/PWM/IO_Protection/VCC_OUT_4: F14.2, JP28.2 (B); also elsewhere on the board
/PWM/IO_Protection/VCC_OUT_5: F15.2, JP29.2 (B); also elsewhere on the board
GND: U14.2, U15.2, U16.2, U17.2; also elsewhere on the board
unnamed: D15.1 (K), R97.1
unnamed: D16.1 (K), R100.1
unnamed: D17.1 (K), R103.1
unnamed: D18.1 (K), R106.1
unnamed: F12.1, JP26.1 (A), U14.4
unnamed: F13.1, JP27.1 (A), U15.4
unnamed: F14.1, JP28.1 (A), U16.4
unnamed: F15.1, JP29.1 (A), U17.4
unnamed: R96.2, U14.1
unnamed: R99.2, U15.1
unnamed: R102.2, U16.1
unnamed: R105.2, U17.1
PWM_M_FL: R99.1; also elsewhere on the board
PWM_M_FR: R96.1; also elsewhere on the board
PWM_M_RL: R105.1; also elsewhere on the board
PWM_M_RR: R102.1; also elsewhere on the board

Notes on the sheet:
V_{f} = 1.3V (LED forward voltage) I_{f(max)} = 50mA R1 = (V_{IN} - V_{f})/I_{f} = (3.3V -1.3V)/5mA = 400Ω --> 470Ω
I_{max} = 100mA @ 5V
I_{max} = 4.26mA @ 3.3V
